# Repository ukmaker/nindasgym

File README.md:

# nindasgym
A 3D printed gym with flashing lights, music and animation

All the gym equipment was printed from [TanyaAkinora's project](https://www.instructables.com/3d-Printed-Tiny-Gym/) - thanks Tanya!

# A Reasonable Excuse
Why do something this silly? Hmm?

The story goes something like this:
  - The Dutch celebrate SinterKlaas on the 5th December as part of their Christmas tradition
  - One of the components of the celebrationis that there is a party
  - Each guest gets assigned (randomly and without the other knowing) another guest
  - The guests then make by hand a small suprise, write an accompanying poem and buy a small present
  - On the 5th, the recipients read their poem and receive their surprise and present
  - I know this because my Dutch neighbour told me, so it must be true
  - This was the second year for us to copy the tradition here in the UK
  - We may have gone a tiny bit overboard

My surprise recipient this year was my friend's sister Ninda who is a personal trainer. I started just with a cardboard box and the 3d printed gym equipment. Then I noticed I had a spare strip of 3-colour LEDS.......

# How Can I Make One?

1. Print the gym bits from Tetiana's project
2. Add extra ingredients
3. Bake until done

# The Recipe
## Ingredients
1. Tetiana's gym equipment
2. A cardboard box
3. Spray paint
4. 3-colour LED lighting strip - lengths to suit your box
5. A suitable power supply. I ended up using an 18V, 2A supply to make sure the stepper motor had enough oomph
6. A stepper motor. You'll need to experiment
7. One Arduino - pretty much anything will do
8. One stepper motor driver - [e.g. this A4988 one](https://reprapworld.co.uk/electronics/3d-printer-modules/stepper-drivers/a4988-stepper-motor-driver-carrier/?f=ms&mkwid=aGITQRal_dc%7Cpcrid%7C72636737008573%7Cpkw%7C%7Cpmt%7Cbe%7Cslid%7C%7Cprid%7CPF_92_8719345011504_POLOLU&pgrid=1162184743076999&ptaid=pla-4576236135429224&msclkid=d0e02402eb9218b8430e47b68c6f800f)
9. One [MP3 player module](https://www.amazon.co.uk/dp/B01N6P237G/ref=pe_27063361_485629781_TE_item)
10.  A small loudspeaker
11. A handful of components as per the schematic
12. You favourite protoyping board
13. Assorted bits of hardware for the lifting mechanism - e.g. small drawer slide, GT2 drive belt, pulley wheels.... 

## Method - Electronics

If you look at all the photos in the assets/ folder you'll see that I constructed the electronics on several small boards for ease of debugging:
 - A board holding the Atmega328 and associated support components. You can replace this directly with an Arduino if you like. I just happen to have a load of 328Ps and crystals etc, so it's cheap and easy for me to do this. I put the MP3 player
 module on this board also
 - A board holding the 7805 regulator and the LED driver transistors. I used ZTX650 transistors because I've had a box of them I'm been slowly getting through since 1980. You can use something more modern like ZTX618 or even 2N7000 (add 100K pull-downs on the gate if you do this).
 - A board holding the A4988 stepper driver

## Method - Mechanics
There was no method. I bodged stuff together until it worked. I had to swap the 12V power supply I was using for an 18V supply
literally at the last minute because the stepper just didn't have the power to lift the lid.

If I was to do this again (stop tittering in the back) I'd actually design it. There would be appropriate gearing.
Vital pieces of mechnanics would be properly attached, not held on with superglue/hotglue/screws through cardboard.

The MCU knows when to stop raising or lowering the lid because there are two microswitches, one at the top of the box and one near the bottom. I 3D printed a T-shaped attachemnt which is stuck to the drive belt and triggers the microswitches. If you look at the image TopEndstop.jpg you will see the wire going to the microswitch which is glued to a 3D printed bracket which is itself stuck to the the side of the box.

## Method - Firmware
I bought a CD copy of the Survivor album, ripped the Eye of the Tiger track and copied it to an SD card which goes in the MP3 player. The CD was part of Ninda's present.

I carefully timed how long it takes to get to the lyric "rising up" and programmed that into the Arduino sketch.

The sketch is triggered when the door is opened because there is a small microswitch which is activated when the door opens.

Closing the door causes the music to stop, the lights stop flashing and glow red and the lid goes back down.

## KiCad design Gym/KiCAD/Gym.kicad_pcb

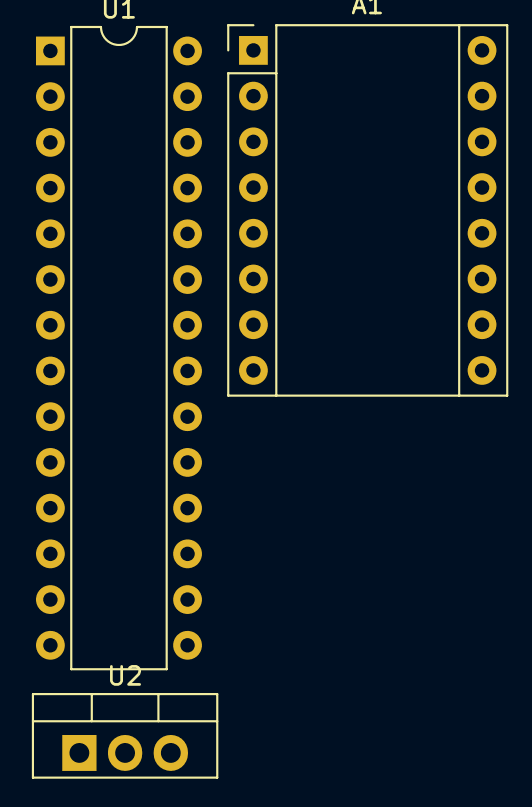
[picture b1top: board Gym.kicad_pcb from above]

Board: 2 copper layers, 3 parts (0 on the bottom side), 6 nets, no tracks yet.

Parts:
A1: Pololu_Breakout_A4988; Pololu_Breakout-16_15.2x20.3mm
U1: ATmega328-P; DIP-28_W7.62mm
U2: LM7805_TO220; TO-220-3_Vertical

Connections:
+5V: A1.2 (VDD), U1.7 (VCC), U1.20 (AVCC), U2.3 (VO)
DIR: A1.16 (DIR), U1.14 (PB0)
GND: A1.1 (GND), A1.7 (GND), U1.8 (GND), U1.22 (GND), U2.2 (GND)
unnamed: A1.8 (VMOT), U2.1 (VI)
unnamed: A1.13 (~RESET), A1.14 (~SLEEP)
STEP: A1.15 (STEP), U1.15 (PB1)

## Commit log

2023-01-03 Initial import
2023-01-03 Added images
2023-01-03 More README upates
2023-01-03 Markdown. A silly idea.
2023-01-03 What did I just say?
2023-01-03 README
2023-01-03 Added schematic PDF and renamed the parent folder
